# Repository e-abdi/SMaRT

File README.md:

# SMaRT
**Sensor Management and Relay Tool**

This tool is designed to facilitate easier sensor integration on gliders, and it replaces [this board](https://github.com/e-abdi/Smart-Cable).
The idea is to have a mainboard that hosts popular, easy-to-source modules in order to create a man-in-the-middle board for custom sensor integration on Seaglider or to fully use the capabilities of the Slocum BackSeatDriver without the need for power-hungry boards such as the Raspberry Pi or other single-board computers.

**Hardware**

- the brain is an RP2040 board (Pi Pico)
- the RS232 transceivers are SparkFun MAX3232 modules
- the DC-DC converter is the popular MP1584 module
- (optional) OpenLog for using this board as a data logger
- (optional) solid-state relay for independent sensor power control
- Connectors:
	- Molex connectors compatible with the ones used in the Slocum Science Computer
	- 2.54 mm pitch footprints for most other connectors, so either simple headers or other locking connectors such as the JST-XH series can be used
	- 2 x Qwiic connectors for connecting external sensor modules

The form factor is also just small enough to fit inside a [1000 m rated 2" x 150 mm Blue Robotics housing](https://bluerobotics.com/store/watertight-enclosures/wte-vp/), so it could be used as an external interface, which was the original idea. It could also be used as a simple logger with a single end connection to a sensor.

**Firmware**

The firmware is based on Zephyr, a modern open-source real-time operating system hosted by the Linux Foundation and originally initiated by Intel. It follows industry best practices for safety, security, and modularity, and benefits from a broad, vendor-neutral ecosystem. Unlike many traditional RTOS solutions that are tightly coupled to a single vendor, Zephyr is highly portable and hardware-agnostic, making it well suited for flexible and scalable embedded system design.
The firmware (see [firmware/README.md](firmware/README.md)) supports both Slocum (Backseat Driver) and Seaglider (logdev). Each glider + sensor integration is a profile under `firmware/profiles/`: a configuration file plus the matching glider-side file (`extctl.ini` or `.cnf`), so most new sensors need no code. Profiles are included for the UVP6 on both gliders. The original Slocum UVP6 firmware is kept in `legacy/uvp6_slocum_v1`.

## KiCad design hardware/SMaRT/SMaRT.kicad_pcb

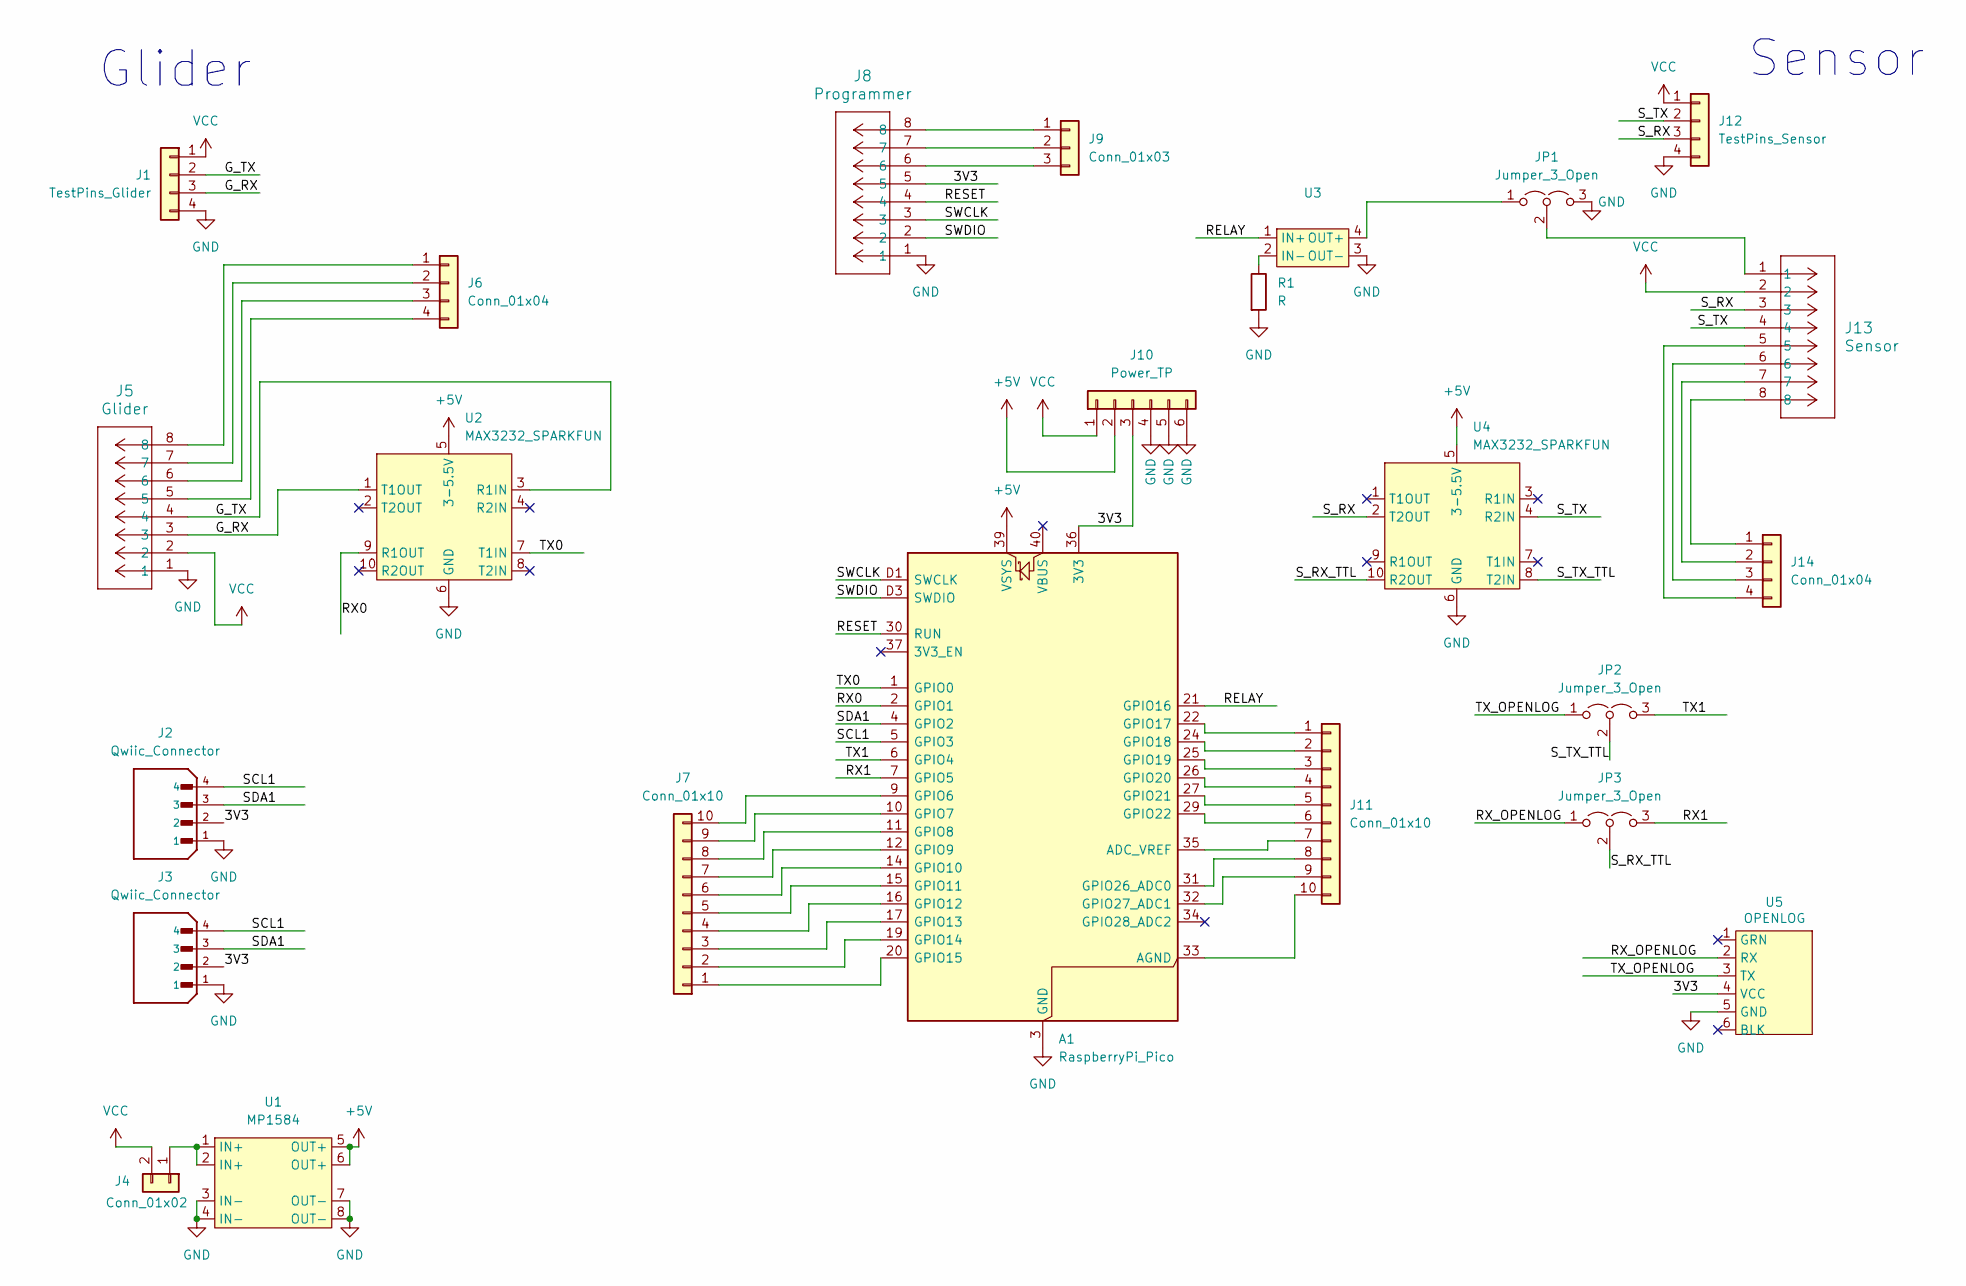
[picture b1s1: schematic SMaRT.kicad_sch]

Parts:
A1: RaspberryPi_Pico; RaspberryPi_Pico_SMD_HandSolder
J1: TestPins_Glider; PinHeader_1x04_P2.54mm_Vertical
J2, J3: Qwiic_Connector; Qwiic; PARTREV NA
J4: Conn_01x02; PinHeader_1x02_P2.54mm_Vertical
J5: Glider; CONN_2068320000-SD_08_MOL
J6, J14: Conn_01x04; PinHeader_1x04_P2.54mm_Vertical
J7, J11: Conn_01x10; PinHeader_1x10_P2.54mm_Vertical
J8: Programmer; CONN_2068320000-SD_08_MOL
J9: Conn_01x03; PinHeader_1x03_P2.54mm_Vertical
J10: Power_TP; PinHeader_1x06_P2.54mm_Vertical
J12: TestPins_Sensor; PinHeader_1x04_P2.54mm_Vertical
J13: Sensor; CONN_2068320000-SD_08_MOL
JP1, JP2, JP3: Jumper_3_Open; PinHeader_1x03_P2.54mm_Vertical
R1: R; R_Axial_DIN0207_L6.3mm_D2.5mm_P7.62mm_Horizontal
U1: MP1584; MPT1584EN_Module
U2, U4: MAX3232_SPARKFUN; MAX3232_Sparkfun
U3: G3VM-41AY1
U5: OPENLOG; OpenLog

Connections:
+5V: A1.39 (VSYS), J10.2, U1.5 (OUT+), U1.6 (OUT+), U2.5 (3-5.5V), U4.5 (3-5.5V)
/3V3: A1.36 (3V3), J2.2, J3.2, J8.5, J10.3, U5.4 (VCC)
/G_RX: J1.3, J5.3, U2.1 (T1OUT)
/G_TX: J1.2, J5.4, U2.3 (R1IN)
/RELAY: A1.21 (GPIO16), U3.1 (IN+)
/RESET: A1.30 (RUN), J8.4
/RX0: A1.2 (GPIO1), U2.9 (R1OUT)
/RX1: A1.7 (GPIO5), JP3.3 (B)
/RX_OPENLOG: JP3.1 (A), U5.2 (RX)
/SCL1: A1.5 (GPIO3), J2.4, J3.4
/SDA1: A1.4 (GPIO2), J2.3, J3.3
/SWCLK: A1.D1 (SWCLK), J8.3
/SWDIO: A1.D3 (SWDIO), J8.2
/S_RX: J12.3, J13.3, U4.2 (T2OUT)
/S_RX_TTL: JP3.2 (C), U4.10 (R2OUT)
/S_TX: J12.2, J13.4, U4.4 (R2IN)
/S_TX_TTL: JP2.2 (C), U4.8 (T2IN)
/TX0: A1.1 (GPIO0), U2.7 (T1IN)
/TX1: A1.6 (GPIO4), JP2.3 (B)
/TX_OPENLOG: JP2.1 (A), U5.3 (TX)
GND: A1.3 (GND), A1.8 (GND), A1.13 (GND), A1.18 (GND), A1.23 (GND), A1.28 (GND), A1.38 (GND), A1.D2 (GND), J1.4, J2.1, J3.1, J5.1, J8.1, J10.4, J10.5, J10.6, J12.4, JP1.3 (B), R1.2, U1.3 (IN-), U1.4 (IN-), U1.7 (OUT-), U1.8 (OUT-), U2.6 (GND), U3.3 (OUT-), U4.6 (GND), U5.5 (GND)
unnamed: A1.35 (ADC_VREF), J11.7
unnamed: A1.33 (AGND), J11.10
unnamed: A1.9 (GPIO6), J7.10
unnamed: A1.10 (GPIO7), J7.9
unnamed: A1.11 (GPIO8), J7.8
unnamed: A1.12 (GPIO9), J7.7
unnamed: A1.14 (GPIO10), J7.6
unnamed: A1.15 (GPIO11), J7.5
unnamed: A1.16 (GPIO12), J7.4
unnamed: A1.17 (GPIO13), J7.3
unnamed: A1.19 (GPIO14), J7.2
unnamed: A1.20 (GPIO15), J7.1
unnamed: A1.22 (GPIO17), J11.1
unnamed: A1.24 (GPIO18), J11.2
unnamed: A1.25 (GPIO19), J11.3
unnamed: A1.26 (GPIO20), J11.4
unnamed: A1.27 (GPIO21), J11.5
unnamed: A1.29 (GPIO22), J11.6
unnamed: A1.31 (GPIO26_ADC0), J11.8
unnamed: A1.32 (GPIO27_ADC1), J11.9
unnamed: J4.1, U1.1 (IN+), U1.2 (IN+)
unnamed: J5.8, J6.1
unnamed: J5.7, J6.2
unnamed: J5.6, J6.3
unnamed: J5.5, J6.4
unnamed: J8.8, J9.1
unnamed: J8.7, J9.2
unnamed: J8.6, J9.3
unnamed: J13.8, J14.1
unnamed: J13.7, J14.2
unnamed: J13.6, J14.3
unnamed: J13.5, J14.4
unnamed: JP1.1 (A), U3.4 (OUT+)
unnamed: J13.1, JP1.2 (C)
unnamed: R1.1, U3.2 (IN-)
VCC: J1.1, J4.2, J5.2, J10.1, J12.1, J13.2

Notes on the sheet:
Sensor
Glider

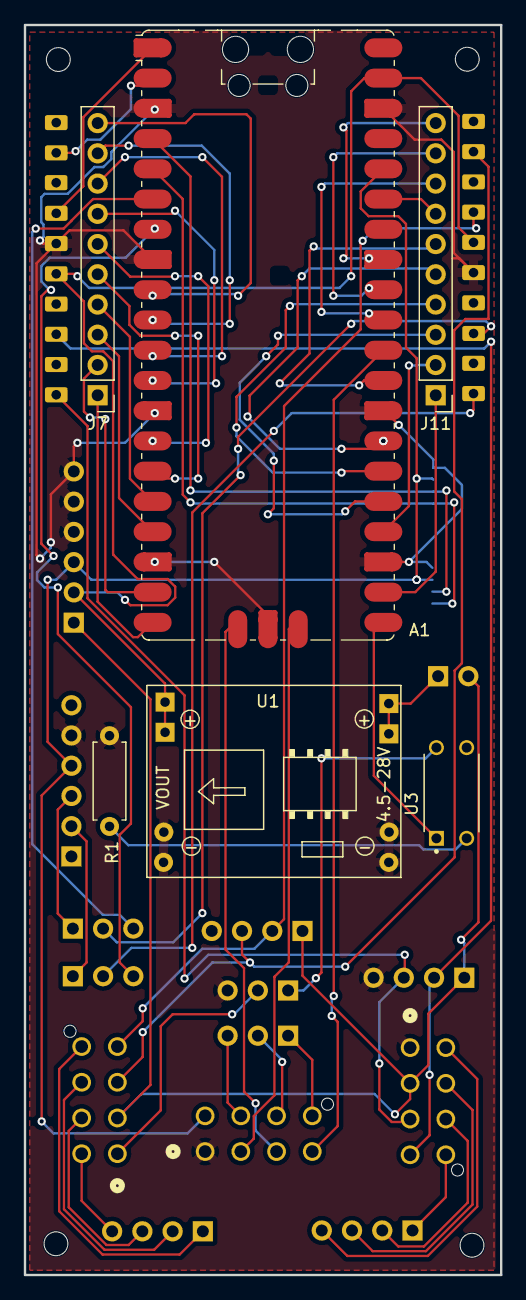
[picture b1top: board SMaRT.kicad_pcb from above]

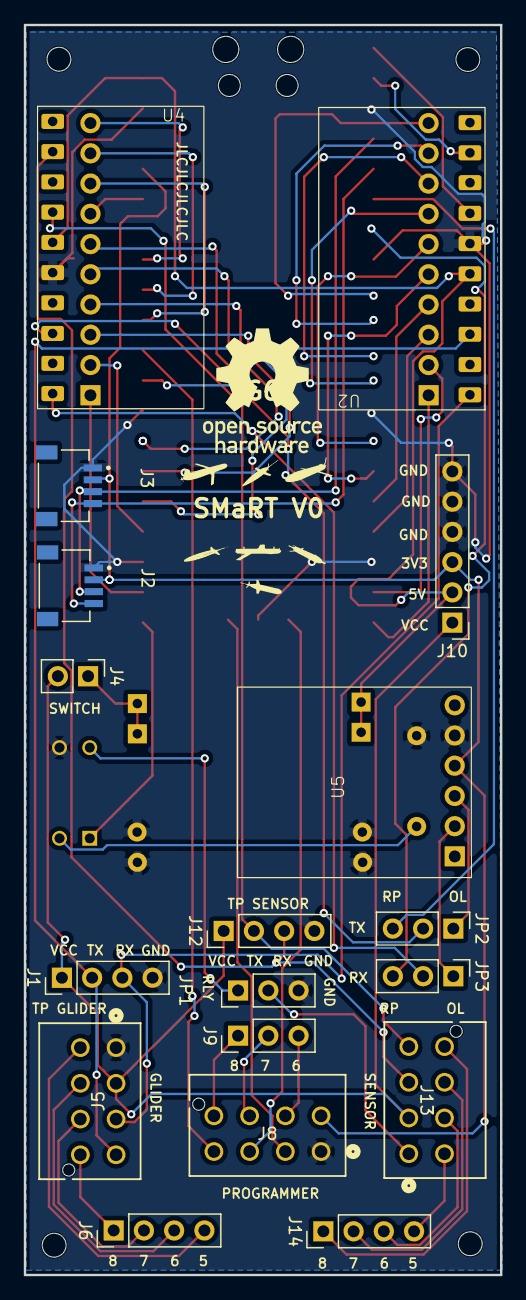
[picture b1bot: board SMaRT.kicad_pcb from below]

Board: 2 copper layers, 40.0 x 105.0 mm, 36 parts (26 on the bottom side), 57 nets.

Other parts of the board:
G1, G2, G3, G4, G5, G6, G7, G8: LOGO
H1, H2, H3, H4: MountingHole_2mm

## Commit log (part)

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2025-10-06 Initial commit: Zephyr Pico app
2026-01-28 Add KiCad hardware project
2026-01-28 edit to gitignore
2026-01-31 added openlog, relay, switch
2026-02-14 relay addition
2026-05-04 hardware: update SMaRT board and ignore KiCad artifacts
2026-05-09 hardware: add mounting holes and power test header
2026-05-25 hardware: update PCB and schematic
2026-05-25 firmware: replace with SMaRT_UVP6_v1 from akvaplan-niva; update README with hardware description and pics
2026-05-25 docs: add Logdev User Guide; minor README whitespace
2026-05-30 docs: improve README grammar
2026-05-30 docs: refine README description
2026-06-03 First version of the SMaRT cabling
2026-06-04 Modifications of the GND connexions
